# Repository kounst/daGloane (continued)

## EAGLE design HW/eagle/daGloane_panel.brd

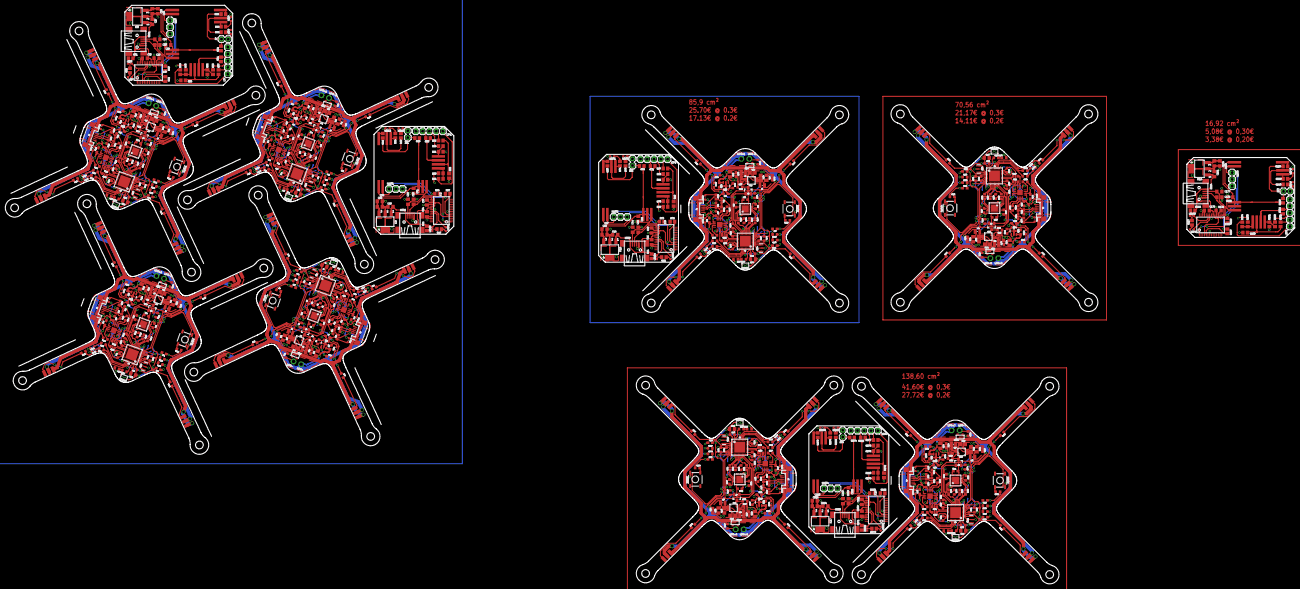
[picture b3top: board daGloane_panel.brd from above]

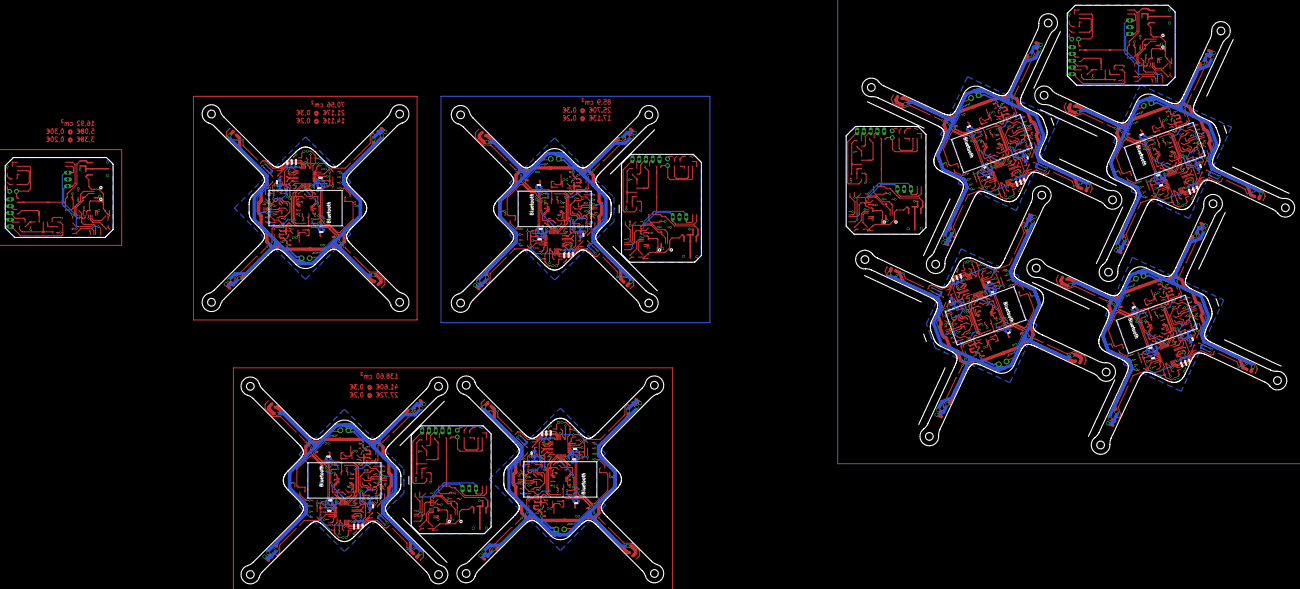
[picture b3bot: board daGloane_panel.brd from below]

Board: 2 copper layers, 484.4 x 217.4 mm, 897 parts (64 on the bottom side), 652 nets.

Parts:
!AT, !AT1, !AT2, !AT3, !AT4: 1X02
BOOTMD, BOOTMD1, BOOTMD2, BOOTMD3, BOOTMD4, BOOTMD5, BOOTMD6, BOOTMD7: 1X02_50MIL
C1, C3, C5, C7, C9, C14, C19, C20, C32, C33, C50, C53, C55, C57, C59, C62, C64, C66, C72, C73, C74, C75, C82, C83, C84, C87, C89, C91, C97, C98, C99, C100, C107, C108, C109, C112, C114, C116, C122, C123, C124, C125, C132, C133, C138, C139, C140, C141, C148, C149, C150, C153, C155, C157, C163, C164, C165, C166, C173, C174, C183, C186, C188, C190, C196, C197, C198, C199, C206, C207, C216, C219, C221, C223, C229, C230, C231, C232, C239, C240: 100nF; C0603
C2, C12, C13, C21, C30, C31, C69, C70, C76, C79, C80, C81, C94, C95, C101, C104, C105, C106, C119, C120, C126, C129, C130, C131, C135, C136, C142, C145, C146, C147, C160, C161, C167, C170, C171, C172, C193, C194, C200, C203, C204, C205, C226, C227, C233, C236, C237, C238: 10µF/6.3V; C0805
C4, C68, C93, C118, C134, C159, C192, C225: 4.7; C0603
C6, C58, C67, C92, C117, C158, C191, C224: 4.7µF; C0603
C8, C10, C71, C78, C96, C103, C121, C128, C137, C144, C162, C169, C195, C202, C228, C235: 1µF; C0603
C11, C16, C54, C63, C77, C88, C102, C113, C127, C143, C154, C168, C187, C201, C220, C234: 10nF; C0603
C15, C56, C65, C90, C115, C156, C189, C222: 2.2nF; C0603
C17, C18, C51, C52, C60, C61, C85, C86, C110, C111, C151, C152, C184, C185, C217, C218: 47pF; C0603
C22, C25, C28, C29, C34, C37, C39, C41, C42, C45, C47, C49, C175, C178, C180, C182, C208, C211, C213, C215: 100nF; C0805
C23, C24, C35, C36, C43, C44, C176, C177, C209, C210: 47pF; C0805
C26, C27, C38, C40, C46, C48, C179, C181, C212, C214: 10µ; C0805
D1, D2, D3, D4, D5, D6, D7, D8: BAT54C; SOT23
GND, GND1, GND2, GND3, GND4, GND5, GND6, GND7: TESTPAD_TPB1,27; TESTPAD_B1,27
IC1, IC4, IC6, IC7, IC11, IC12, IC15, IC18: MCP1252-33X50; MSOP8
IC2, IC3, IC9, IC13, IC16: FT232RL; SSOP28DB
IC5, IC8, IC10, IC14, IC17: UA78M05DCY; SOT223
L1, L2, L3, L4, L5, L6, L7, L8, L9, L10, L11, L12, L13, L14, L15, L16: WUERTH-ELEKTRONIK_WE-KI_0805_B
LED1, LED2, LED3, LED4, LED5, LED6, LED7, LED8, LED9, LED10, LED11, LED12, LED13, LED14, LED15, LED16, LED17, LED18, LED19, LED20, LED21, LED22, LED23, LED24, LED25, LED26, LED27, LED28, LED29, LED30, LED31, LED32, LED33, LED34, LED35, LED36, LED37, LED38, LED39, LED40, LED41, LED42, LED43, LED44, LED45, LED46, LED47, LED48, LED49, LED50, LED51, LED52, LED53, LED54, LED55, LED56, LED57, LED58, LED59, LED60: CHIPLED_0603
LIPO+, LIPO+1, LIPO+2, LIPO+3, LIPO+4, LIPO+5, LIPO+6, LIPO+7: TPSPAD1-13; P1-13
LIPO-, LIPO-1, LIPO-2, LIPO-3, LIPO-4, LIPO-5, LIPO-6, LIPO-7: TPSPAD1-13; P1-13
LTP, LTP1, LTP2, LTP3, LTP4: 1X05
ON/OFF, ON/OFF1, ON/OFF2, ON/OFF3, ON/OFF4, ON/OFF5, ON/OFF6, ON/OFF7: SWITCH-MOMENTARY-2SMD; TACTILE_SWITCH_SMD
R1, R3, R4, R5, R14, R15, R16, R19, R76, R81, R82, R83, R86, R87, R88, R89, R106, R111, R112, R113, R116, R117, R118, R119, R136, R141, R142, R143, R146, R147, R148, R149, R166, R171, R172, R173, R176, R177, R178, R179, R196, R201, R202, R203, R206, R207, R208, R209, R241, R246, R247, R248, R251, R252, R253, R254, R286, R291, R292, R293, R296, R297, R298, R299: 150R; R0603
R2, R92, R122, R152, R182, R212, R257, R302: 2k; R0603
R6, R7, R8, R17, R18, R20, R24, R25, R26, R27, R28, R77, R78, R93, R94, R95, R98, R100, R101, R102, R103, R104, R107, R108, R123, R124, R125, R128, R130, R131, R132, R133, R134, R137, R138, R153, R154, R155, R158, R160, R161, R162, R163, R164, R167, R168, R183, R184, R185, R188, R190, R191, R192, R193, R194, R197, R198, R213, R214, R215, R218, R220, R221, R222, R223, R224, R242, R243, R258, R259, R260, R263, R265, R266, R267, R268, R269, R287, R288, R303, R304, R305, R308, R310, R311, R312, R313, R314: 10k; R0603
R9, R10, R12, R22, R23, R30, R79, R90, R91, R96, R97, R105, R109, R120, R121, R126, R127, R135, R139, R150, R151, R156, R157, R165, R169, R180, R181, R186, R187, R195, R199, R210, R211, R216, R217, R225, R244, R255, R256, R261, R262, R270, R289, R300, R301, R306, R307, R315: 1k; R0603
R11, R13, R84, R85, R114, R115, R144, R145, R174, R175, R204, R205, R249, R250, R294, R295: 27R; R0603
R21, R80, R110, R140, R170, R200, R245, R290: 3k3; R0603
R29, R99, R129, R159, R189, R219, R264, R309: 330; R0603
R31, R32, R46, R47, R61, R62, R226, R227, R271, R272: 150R; R0805
R33, R34, R42, R43, R48, R49, R57, R58, R63, R64, R72, R73, R228, R229, R237, R238, R273, R274, R282, R283: 4k7; R0805
R35, R37, R39, R50, R52, R54, R65, R67, R69, R230, R232, R234, R275, R277, R279: 1k6; R0805
R36, R38, R40, R51, R53, R55, R66, R68, R70, R231, R233, R235, R276, R278, R280: 3k; R0805
R41, R56, R71, R236, R281: 100; R0805
R44, R45, R59, R60, R74, R75, R239, R240, R284, R285: 470R; R0805
SWCLK, SWCLK1, SWCLK2, SWCLK3, SWCLK4, SWCLK5, SWCLK6, SWCLK7: TESTPAD_TPB1,27; TESTPAD_B1,27
SWDIO, SWDIO1, SWDIO2, SWDIO3, SWDIO4, SWDIO5, SWDIO6, SWDIO7: TESTPAD_TPB1,27; TESTPAD_B1,27
U1, U2, U3, U4, U5, U6, U7, U8: STM32F10XTXU6; VFQFPN36
U$1, U$38, U$49, U$60, U$84, U$95, U$118, U$141: MURATA-FILTER_CSTCE__G
U$2, U$37, U$48, U$59, U$83, U$94, U$117, U$140: SPARKFUN_MCP73831; SPARKFUN_SOT23-5
U$3, U$35, U$46, U$57, U$81, U$92, U$115, U$138: MPU6000
U$4, U$36, U$47, U$58, U$82, U$93, U$116, U$139: SERIAL_FT230XQ; SERIAL_QFN4X4-16
U$5, U$40, U$51, U$62, U$86, U$97, U$120, U$143: BLUETOOTH_REDUCED
U$6, U$7, U$8, U$9, U$41, U$42, U$43, U$44, U$52, U$53, U$54, U$55, U$63, U$64, U$65, U$66, U$87, U$88, U$89, U$90, U$98, U$99, U$100, U$101, U$121, U$122, U$123, U$124, U$144, U$145, U$146, U$147: 3A_BLDC_CONTROLLER
U$10, U$39, U$50, U$61, U$85, U$96, U$119, U$142: IRLM6344TRPBF; MICRO3(SOT-23)
U$11, U$45, U$56, U$67, U$91, U$102, U$125, U$148: DAGLOANE_LOGO
U$12, U$13, U$14, U$15, U$16, U$17, U$18, U$19, U$20, U$21, U$22, U$23, U$24, U$25, U$26, U$27, U$28, U$29, U$30, U$31, U$32, U$33, U$34, U$68, U$69, U$70, U$71, U$72, U$73, U$74, U$75, U$76, U$77, U$78, U$79, U$80, U$103, U$104, U$105, U$106, U$107, U$108, U$109, U$110, U$111, U$112, U$113, U$114, U$126, U$127, U$128, U$129, U$130, U$131, U$132, U$133, U$134, U$135, U$136, U$137: SPRING_HEADER
UART, UART1, UART2, UART3, UART4: 1X03
USB1, USB2, USB3, USB4, USB5: USB-MB-S2; USB-MP-S2
X1, X2, X3, X4, X5, X6, X7, X8: USB_MICROB_PLUG_MT; SPARKFUN-CONNECTORS_USB-MICROB

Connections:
+3V1: C38.1, C39.1, C41.1, IC8.3, R49.2, U$26.P$1, U$30.P$1
+3V2: C46.1, C47.1, C49.1, IC10.3, R64.2, U$71.P$1, U$75.P$1
+3V3: C26.1, C28.1, C29.1, IC5.3, R34.2, U$14.P$1, U$18.P$1
+3V4: C179.1, C180.1, C182.1, IC14.3, R229.2, U$105.P$1, U$109.P$1
+3V5: C212.1, C213.1, C215.1, IC17.3, R274.2, U$128.P$1, U$132.P$1
BOOT0: R17.1, U1.35
BOOT1: R168.1, U2.35
BOOT2: R78.1, U3.35
BOOT3: R108.1, U4.35
BOOT4: R138.1, U5.35
BOOT5: R198.1, U6.35
BOOT6: R243.1, U7.35
BOOT7: R288.1, U8.35
CLK: LTP.3, R35.2
CLK1: LTP1.3, R50.2
CLK2: LTP2.3, R65.2
CLK3: LTP3.3, R230.2
CLK4: LTP4.3, R275.2
CSB: LTP.5, R39.2
CSB1: LTP1.5, R54.2
CSB2: LTP2.5, R69.2
CSB3: LTP3.5, R234.2
CSB4: LTP4.5, R279.2
D+: C18.1, R13.1, X2.D+
D+1: C23.1, IC3.15, USB1.D+
D+2: C35.1, IC2.15, USB2.D+
D+3: C60.1, R85.1, X3.D+
D+4: C85.1, R115.1, X4.D+
D+5: C110.1, R145.1, X5.D+
D+6: C43.1, IC9.15, USB3.D+
D+7: C51.1, R175.1, X1.D+
D+8: C151.1, R205.1, X6.D+
D+9: C176.1, IC13.15, USB4.D+
D+10: C184.1, R250.1, X7.D+
D+11: C209.1, IC16.15, USB5.D+
D+12: C217.1, R295.1, X8.D+
D-: C17.1, R11.1, X2.D-
D-1: C24.1, IC3.16, USB1.D-
D-2: C36.1, IC2.16, USB2.D-
D-3: C61.1, R84.1, X3.D-
D-4: C86.1, R114.1, X4.D-
D-5: C111.1, R144.1, X5.D-
D-6: C44.1, IC9.16, USB3.D-
D-7: C52.1, R174.1, X1.D-
D-8: C152.1, R204.1, X6.D-
D-9: C177.1, IC13.16, USB4.D-
D-10: C185.1, R249.1, X7.D-
D-11: C210.1, IC16.16, USB5.D-
D-12: C218.1, R294.1, X8.D-
GND: C1.2, C2.2, C3.2, C4.2, C5.2, C6.1, C7.2, C9.1, C10.2, C11.2, C12.2, C13.2, C14.2, C15.2, C16.2, C17.2, C18.2, C19.2, C20.2, C21.2, C30.2, C31.2, C32.1, C33.1, GND.PP, IC1.4, LED3.C, LED4.C, LIPO-.TP, R2.2, R7.1, R8.1, R20.1, R21.1, R24.1, R28.1, U1.5, U1.18, U1.26, U1.36, U$1.2, U$2.2, U$3.1, U$3.11, U$3.18, U$4.3, U$4.13, U$4.C, U$5.P$13, U$5.P$14, U$5.P$21, U$5.P$22, U$10.2, X2.GND
GND1: !AT.2, C22.1, C23.2, C24.2, C25.2, C26.2, C27.2, C28.2, C29.2, IC3.7, IC3.18, IC3.21, IC3.25, IC3.26, IC5.2, IC5.4, LED8.C, LED9.C, LTP.1, R36.1, R38.1, R40.1, U$15.P$1, UART.2, USB1.GND
GND2: !AT1.2, C34.1, C35.2, C36.2, C37.2, C38.2, C39.2, C40.2, C41.2, IC2.7, IC2.18, IC2.21, IC2.25, IC2.26, IC8.2, IC8.4, LED12.C, LED13.C, LTP1.1, R51.1, R53.1, R55.1, U$27.P$1, UART1.2, USB2.GND
GND3: C59.2, C60.2, C61.2, C62.2, C63.2, C64.2, C65.2, C66.2, C67.1, C68.2, C69.2, C70.2, C72.1, C73.2, C74.2, C75.2, C76.2, C77.2, C78.2, C79.2, C80.2, C81.2, C82.1, C83.1, GND2.PP, IC4.4, LED15.C, LED16.C, LIPO-2.TP, R77.1, R80.1, R92.2, R93.1, R95.1, R98.1, R104.1, U3.5, U3.18, U3.26, U3.36, U$35.1, U$35.11, U$35.18, U$36.3, U$36.13, U$36.C, U$37.2, U$38.2, U$39.2, U$40.P$13, U$40.P$14, U$40.P$21, U$40.P$22, X3.GND
GND4: C84.2, C85.2, C86.2, C87.2, C88.2, C89.2, C90.2, C91.2, C92.1, C93.2, C94.2, C95.2, C97.1, C98.2, C99.2, C100.2, C101.2, C102.2, C103.2, C104.2, C105.2, C106.2, C107.1, C108.1, GND3.PP, IC6.4, LED20.C, LED21.C, LIPO-3.TP, R107.1, R110.1, R122.2, R123.1, R125.1, R128.1, R134.1, U4.5, U4.18, U4.26, U4.36, U$46.1, U$46.11, U$46.18, U$47.3, U$47.13, U$47.C, U$48.2, U$49.2, U$50.2, U$51.P$13, U$51.P$14, U$51.P$21, U$51.P$22, X4.GND
GND5: C109.2, C110.2, C111.2, C112.2, C113.2, C114.2, C115.2, C116.2, C117.1, C118.2, C119.2, C120.2, C122.1, C123.2, C124.2, C125.2, C126.2, C127.2, C128.2, C129.2, C130.2, C131.2, C132.1, C133.1, GND4.PP, IC7.4, LED25.C, LED26.C, LIPO-4.TP, R137.1, R140.1, R152.2, R153.1, R155.1, R158.1, R164.1, U5.5, U5.18, U5.26, U5.36, U$57.1, U$57.11, U$57.18, U$58.3, U$58.13, U$58.C, U$59.2, U$60.2, U$61.2, U$62.P$13, U$62.P$14, U$62.P$21, U$62.P$22, X5.GND
GND6: !AT2.2, C42.1, C43.2, C44.2, C45.2, C46.2, C47.2, C48.2, C49.2, IC9.7, IC9.18, IC9.21, IC9.25, IC9.26, IC10.2, IC10.4, LED31.C, LED32.C, LTP2.1, R66.1, R68.1, R70.1, U$72.P$1, UART2.2, USB3.GND
GND7: C50.2, C51.2, C52.2, C53.2, C54.2, C55.2, C56.2, C57.2, C58.1, C134.2, C135.2, C136.2, C138.1, C139.2, C140.2, C141.2, C142.2, C143.2, C144.2, C145.2, C146.2, C147.2, C148.1, C149.1, GND1.PP, IC11.4, LED33.C, LED34.C, LIPO-1.TP, R167.1, R170.1, R182.2, R183.1, R185.1, R188.1, R194.1, U2.5, U2.18, U2.26, U2.36, U$81.1, U$81.11, U$81.18, U$82.3, U$82.13, U$82.C, U$83.2, U$84.2, U$85.2, U$86.P$13, U$86.P$14, U$86.P$21, U$86.P$22, X1.GND
GND8: C150.2, C151.2, C152.2, C153.2, C154.2, C155.2, C156.2, C157.2, C158.1, C159.2, C160.2, C161.2, C163.1, C164.2, C165.2, C166.2, C167.2, C168.2, C169.2, C170.2, C171.2, C172.2, C173.1, C174.1, GND5.PP, IC12.4, LED38.C, LED39.C, LIPO-5.TP, R197.1, R200.1, R212.2, R213.1, R215.1, R218.1, R224.1, U6.5, U6.18, U6.26, U6.36, U$92.1, U$92.11, U$92.18, U$93.3, U$93.13, U$93.C, U$94.2, U$95.2, U$96.2, U$97.P$13, U$97.P$14, U$97.P$21, U$97.P$22, X6.GND
GND9: !AT3.2, C175.1, C176.2, C177.2, C178.2, C179.2, C180.2, C181.2, C182.2, IC13.7, IC13.18, IC13.21, IC13.25, IC13.26, IC14.2, IC14.4, LED45.C, LED46.C, LTP3.1, R231.1, R233.1, R235.1, U$106.P$1, UART3.2, USB4.GND
GND10: C183.2, C184.2, C185.2, C186.2, C187.2, C188.2, C189.2, C190.2, C191.1, C192.2, C193.2, C194.2, C196.1, C197.2, C198.2, C199.2, C200.2, C201.2, C202.2, C203.2, C204.2, C205.2, C206.1, C207.1, GND6.PP, IC15.4, LED47.C, LED48.C, LIPO-6.TP, R242.1, R245.1, R257.2, R258.1, R260.1, R263.1, R269.1, U7.5, U7.18, U7.26, U7.36, U$115.1, U$115.11, U$115.18, U$116.3, U$116.13, U$116.C, U$117.2, U$118.2, U$119.2, U$120.P$13, U$120.P$14, U$120.P$21, U$120.P$22, X7.GND
GND11: !AT4.2, C208.1, C209.2, C210.2, C211.2, C212.2, C213.2, C214.2, C215.2, IC16.7, IC16.18, IC16.21, IC16.25, IC16.26, IC17.2, IC17.4, LED54.C, LED55.C, LTP4.1, R276.1, R278.1, R280.1, U$129.P$1, UART4.2, USB5.GND
GND12: C216.2, C217.2, C218.2, C219.2, C220.2, C221.2, C222.2, C223.2, C224.1, C225.2, C226.2, C227.2, C229.1, C230.2, C231.2, C232.2, C233.2, C234.2, C235.2, C236.2, C237.2, C238.2, C239.1, C240.1, GND7.PP, IC18.4, LED56.C, LED57.C, LIPO-7.TP, R287.1, R290.1, R302.2, R303.1, R305.1, R308.1, R314.1, U8.5, U8.18, U8.26, U8.36, U$138.1, U$138.11, U$138.18, U$139.3, U$139.13, U$139.C, U$140.2, U$141.2, U$142.2, U$143.P$13, U$143.P$14, U$143.P$21, U$143.P$22, X8.GND
LED1: R15.2, U1.30
LED2: R16.2, U1.29
LED3: R171.2, U2.30
LED4: R166.2, U2.29
LED5: R81.2, U3.30
LED6: R76.2, U3.29
LED7: R111.2, U4.30
LED8: R106.2, U4.29
LED9: R141.2, U5.30
LED10: R136.2, U5.29
LED11: R201.2, U6.30
LED12: R196.2, U6.29
LED13: R246.2, U7.30
LED14: R241.2, U7.29
LED15: R291.2, U8.30
LED16: R286.2, U8.29
LIPO: C4.1, C30.1, C32.2, IC1.8, L2.2, LIPO+.TP, ON/OFF.3, R12.2, U$2.3, U$6.2, U$7.2, U$8.2, U$9.2
LIPO1: C134.1, C146.1, C148.2, IC11.8, L4.2, LIPO+1.TP, ON/OFF1.3, R169.2, U$83.3, U$87.2, U$88.2, U$89.2, U$90.2
LIPO2: C68.1, C80.1, C82.2, IC4.8, L6.2, LIPO+2.TP, ON/OFF2.3, R79.2, U$37.3, U$41.2, U$42.2, U$43.2, U$44.2
LIPO3: C93.1, C105.1, C107.2, IC6.8, L8.2, LIPO+3.TP, ON/OFF3.3, R109.2, U$48.3, U$52.2, U$53.2, U$54.2, U$55.2
LIPO4: C118.1, C130.1, C132.2, IC7.8, L10.2, LIPO+4.TP, ON/OFF4.3, R139.2, U$59.3, U$63.2, U$64.2, U$65.2, U$66.2
LIPO5: C159.1, C171.1, C173.2, IC12.8, L12.2, LIPO+5.TP, ON/OFF5.3, R199.2, U$94.3, U$98.2, U$99.2, U$100.2, U$101.2
LIPO6: C192.1, C204.1, C206.2, IC15.8, L14.2, LIPO+6.TP, ON/OFF6.3, R244.2, U$117.3, U$121.2, U$122.2, U$123.2, U$124.2
LIPO7: C225.1, C237.1, C239.2, IC18.8, L16.2, LIPO+7.TP, ON/OFF7.3, R289.2, U$140.3, U$144.2, U$145.2, U$146.2, U$147.2
MISO: LTP.2, R41.2
MISO1: LTP1.2, R56.2
MISO2: LTP2.2, R71.2
MISO3: LTP3.2, R236.2
MISO4: LTP4.2, R281.2
MOSI: LTP.4, R37.2
MOSI1: LTP1.4, R52.2
MOSI2: LTP2.4, R67.2
MOSI3: LTP3.4, R232.2
MOSI4: LTP4.4, R277.2
MOT1: R18.1, U1.15
MOT2: R27.1, U1.16
MOT3: R25.1, U1.31
MOT4: R26.1, U1.32
MOT5: R192.1, U2.32
MOT6: R190.1, U2.15
MOT7: R193.1, U2.16
MOT8: R191.1, U2.31
MOT9: R102.1, U3.32
MOT10: R100.1, U3.15
MOT11: R103.1, U3.16
MOT12: R101.1, U3.31
MOT13: R132.1, U4.32
MOT14: R130.1, U4.15
MOT15: R133.1, U4.16
MOT16: R131.1, U4.31
MOT17: R162.1, U5.32
MOT18: R160.1, U5.15
MOT19: R163.1, U5.16
MOT20: R161.1, U5.31
MOT21: R222.1, U6.32
MOT22: R220.1, U6.15
MOT23: R223.1, U6.16
MOT24: R221.1, U6.31
MOT25: R267.1, U7.32
MOT26: R265.1, U7.15
MOT27: R268.1, U7.16
MOT28: R266.1, U7.31
MOT29: R312.1, U8.32
MOT30: R310.1, U8.15
MOT31: R313.1, U8.16
MOT32: R311.1, U8.31
MOT_GND: U$6.1, U$7.1, U$8.1, U$9.1, U$10.3
MOT_GND1: U$85.3, U$87.1, U$88.1, U$89.1, U$90.1
MOT_GND2: U$39.3, U$41.1, U$42.1, U$43.1, U$44.1
MOT_GND3: U$50.3, U$52.1, U$53.1, U$54.1, U$55.1
MOT_GND4: U$61.3, U$63.1, U$64.1, U$65.1, U$66.1
MOT_GND5: U$96.3, U$98.1, U$99.1, U$100.1, U$101.1
MOT_GND6: U$119.3, U$121.1, U$122.1, U$123.1, U$124.1
MOT_GND7: U$142.3, U$144.1, U$145.1, U$146.1, U$147.1
unnamed: LED2.C, R19.2
unnamed: U1.2, U$1.3
unnamed: R2.1, U$2.5
unnamed: R5.2, U$3.8
unnamed: C15.1, U$3.20
unnamed: C14.1, U$3.10
unnamed: R22.2, U$5.P$1
unnamed: LED3.A, R15.1
unnamed: LED4.A, R16.1
unnamed: BOOTMD.2, R17.2, R20.2
unnamed: R14.1, U$4.11
unnamed: R19.1, U$4.5
unnamed: R4.2, U$3.23
unnamed: LED1.C, R14.2
unnamed: R23.2, U$5.P$2
unnamed: R11.2, U$4.7
unnamed: R13.2, U$4.6
unnamed: R3.2, U$3.9
unnamed: R1.2, U$3.24
unnamed: R9.1, U$4.15
unnamed: R10.1, U$4.2
unnamed: R18.2, U$6.3
unnamed: D3.2, ON/OFF.1, R6.1, R7.2
unnamed: C8.2, IC1.6
unnamed: U1.3, U$1.1
unnamed: R30.1, U$5.P$34
unnamed: IC3.23, LED6.C
unnamed: C8.1, IC1.5
unnamed: IC3.22, LED7.C
unnamed: LED6.A, R31.1
unnamed: LED7.A, R32.1
unnamed: R33.1, U$21.P$1
unnamed: !AT.1, R33.2, R34.1
unnamed: R39.1, R40.2, U$17.P$1
unnamed: R37.1, R38.2, U$19.P$1
unnamed: R35.1, R36.2, U$20.P$1
unnamed: R41.1, U$16.P$1
unnamed: R27.2, U$7.3
unnamed: R25.2, U$8.3
unnamed: R26.2, U$9.3
unnamed: R42.1, U$12.P$1, UART.3
unnamed: R29.2, U$2.1
unnamed: LED5.C, R29.1
unnamed: C12.1, IC1.3, L2.1
unnamed: C13.1, IC1.2, L1.2
unnamed: R43.1, U$13.P$1, UART.1
unnamed: LED8.A, R44.1
unnamed: LED9.A, R45.1
unnamed: R44.2, U$23.P$1
unnamed: R45.2, U$22.P$1
unnamed: IC2.23, LED10.C
unnamed: IC2.22, LED11.C
unnamed: LED10.A, R46.1
unnamed: LED11.A, R47.1
unnamed: R48.1, U$33.P$1
unnamed: !AT1.1, R48.2, R49.1
unnamed: R54.1, R55.2, U$29.P$1
unnamed: R52.1, R53.2, U$31.P$1
unnamed: R50.1, R51.2, U$32.P$1
unnamed: R56.1, U$28.P$1
unnamed: R57.1, U$24.P$1, UART1.3
unnamed: R58.1, U$25.P$1, UART1.1
unnamed: LED12.A, R59.1
unnamed: LED13.A, R60.1
unnamed: R59.2, U$68.P$1
unnamed: R60.2, U$34.P$1
unnamed: IC9.23, LED14.C
unnamed: IC9.22, LED30.C
unnamed: LED14.A, R61.1
unnamed: LED30.A, R62.1
unnamed: R63.1, U$78.P$1
unnamed: !AT2.1, R63.2, R64.1
unnamed: R69.1, R70.2, U$74.P$1
unnamed: R67.1, R68.2, U$76.P$1
unnamed: R65.1, R66.2, U$77.P$1
unnamed: R71.1, U$73.P$1
unnamed: R72.1, U$69.P$1, UART2.3
unnamed: R73.1, U$70.P$1, UART2.1
unnamed: LED31.A, R74.1
unnamed: LED32.A, R75.1
unnamed: R74.2, U$80.P$1
unnamed: R75.2, U$79.P$1
unnamed: BOOTMD1.2, R167.2, R168.2
unnamed: BOOTMD2.2, R77.2, R78.2
unnamed: LED16.A, R76.1
unnamed: LED15.A, R81.1
unnamed: R82.1, U$36.11
unnamed: R83.1, U$36.5
unnamed: R84.2, U$36.7
unnamed: R85.2, U$36.6
unnamed: C65.1, U$35.20
unnamed: C66.1, U$35.10
unnamed: R89.2, U$35.8
unnamed: R88.2, U$35.23
unnamed: R87.2, U$35.9
unnamed: R86.2, U$35.24
unnamed: R90.1, U$36.15
unnamed: R91.1, U$36.2
unnamed: R92.1, U$37.5
unnamed: C71.1, IC4.5
unnamed: C71.2, IC4.6
unnamed: D2.2, ON/OFF2.1, R93.2, R94.1
unnamed: U3.2, U$38.3
unnamed: U3.3, U$38.1
unnamed: LED18.C, R83.2
unnamed: LED17.C, R82.2
unnamed: R96.2, U$40.P$1
unnamed: R97.2, U$40.P$2
unnamed: R99.2, U$37.1
unnamed: LED19.C, R99.1
unnamed: C70.1, IC4.3, L6.1
unnamed: C69.1, IC4.2, L5.2
unnamed: R100.2, U$41.3
unnamed: R103.2, U$42.3
unnamed: R101.2, U$43.3
unnamed: R102.2, U$44.3
unnamed: R105.1, U$40.P$34
unnamed: BOOTMD3.2, R107.2, R108.2
unnamed: LED21.A, R106.1
unnamed: LED20.A, R111.1
unnamed: R112.1, U$47.11
unnamed: R113.1, U$47.5
unnamed: R114.2, U$47.7
unnamed: R115.2, U$47.6
unnamed: C90.1, U$46.20
unnamed: C91.1, U$46.10
unnamed: R119.2, U$46.8
unnamed: R118.2, U$46.23
unnamed: R117.2, U$46.9
unnamed: R116.2, U$46.24
unnamed: R120.1, U$47.15
unnamed: R121.1, U$47.2
unnamed: R122.1, U$48.5
unnamed: C96.1, IC6.5
unnamed: C96.2, IC6.6
unnamed: D4.2, ON/OFF3.1, R123.2, R124.1
unnamed: U4.2, U$49.3
unnamed: U4.3, U$49.1
unnamed: LED23.C, R113.2
unnamed: LED22.C, R112.2
unnamed: R126.2, U$51.P$1
unnamed: R127.2, U$51.P$2
unnamed: R129.2, U$48.1
unnamed: LED24.C, R129.1
unnamed: C95.1, IC6.3, L8.1
unnamed: C94.1, IC6.2, L7.2
unnamed: R130.2, U$52.3
unnamed: R133.2, U$53.3
unnamed: R131.2, U$54.3
unnamed: R132.2, U$55.3
unnamed: R135.1, U$51.P$34
unnamed: BOOTMD4.2, R137.2, R138.2
unnamed: LED26.A, R136.1
unnamed: LED25.A, R141.1
unnamed: R142.1, U$58.11
unnamed: R143.1, U$58.5
unnamed: R144.2, U$58.7
unnamed: R145.2, U$58.6
unnamed: C115.1, U$57.20
unnamed: C116.1, U$57.10
unnamed: R149.2, U$57.8
unnamed: R148.2, U$57.23
unnamed: R147.2, U$57.9
unnamed: R146.2, U$57.24
unnamed: R150.1, U$58.15
unnamed: R151.1, U$58.2
unnamed: R152.1, U$59.5
unnamed: C121.1, IC7.5
unnamed: C121.2, IC7.6
unnamed: D5.2, ON/OFF4.1, R153.2, R154.1
unnamed: U5.2, U$60.3
unnamed: U5.3, U$60.1
unnamed: LED28.C, R143.2
unnamed: LED27.C, R142.2
unnamed: R156.2, U$62.P$1
unnamed: R157.2, U$62.P$2
unnamed: R159.2, U$59.1
unnamed: LED29.C, R159.1
unnamed: C120.1, IC7.3, L10.1
unnamed: C119.1, IC7.2, L9.2
unnamed: R160.2, U$63.3
unnamed: R163.2, U$64.3
unnamed: R161.2, U$65.3
unnamed: R162.2, U$66.3
unnamed: R165.1, U$62.P$34
unnamed: LED34.A, R166.1
unnamed: LED33.A, R171.1
unnamed: R172.1, U$82.11
unnamed: R173.1, U$82.5
unnamed: R174.2, U$82.7
unnamed: R175.2, U$82.6
unnamed: C56.1, U$81.20
unnamed: C57.1, U$81.10
unnamed: R179.2, U$81.8
unnamed: R178.2, U$81.23
unnamed: R177.2, U$81.9
unnamed: R176.2, U$81.24
unnamed: R180.1, U$82.15
unnamed: R181.1, U$82.2
unnamed: R182.1, U$83.5
unnamed: C137.1, IC11.5
unnamed: C137.2, IC11.6
unnamed: D1.2, ON/OFF1.1, R183.2, R184.1
unnamed: U2.2, U$84.3
unnamed: U2.3, U$84.1
unnamed: LED36.C, R173.2
unnamed: LED35.C, R172.2
unnamed: R186.2, U$86.P$1
unnamed: R187.2, U$86.P$2
unnamed: R189.2, U$83.1
unnamed: LED37.C, R189.1
unnamed: C136.1, IC11.3, L4.1
unnamed: C135.1, IC11.2, L3.2
unnamed: R190.2, U$87.3
unnamed: R193.2, U$88.3
unnamed: R191.2, U$89.3
unnamed: R192.2, U$90.3
unnamed: R195.1, U$86.P$34
unnamed: BOOTMD5.2, R197.2, R198.2
unnamed: LED39.A, R196.1
unnamed: LED38.A, R201.1
unnamed: R202.1, U$93.11
unnamed: R203.1, U$93.5
unnamed: R204.2, U$93.7
unnamed: R205.2, U$93.6
unnamed: C156.1, U$92.20
unnamed: C157.1, U$92.10
unnamed: R209.2, U$92.8
unnamed: R208.2, U$92.23
unnamed: R207.2, U$92.9
unnamed: R206.2, U$92.24
unnamed: R210.1, U$93.15
unnamed: R211.1, U$93.2
unnamed: R212.1, U$94.5
unnamed: C162.1, IC12.5
unnamed: C162.2, IC12.6
unnamed: D6.2, ON/OFF5.1, R213.2, R214.1
unnamed: U6.2, U$95.3
unnamed: U6.3, U$95.1
unnamed: LED41.C, R203.2
unnamed: LED40.C, R202.2
unnamed: R216.2, U$97.P$1
unnamed: R217.2, U$97.P$2
unnamed: R219.2, U$94.1
unnamed: LED42.C, R219.1
unnamed: C161.1, IC12.3, L12.1
unnamed: C160.1, IC12.2, L11.2
unnamed: R220.2, U$98.3
unnamed: R223.2, U$99.3
unnamed: R221.2, U$100.3
unnamed: R222.2, U$101.3
unnamed: R225.1, U$97.P$34
unnamed: IC13.23, LED43.C
unnamed: IC13.22, LED44.C
unnamed: LED43.A, R226.1
unnamed: LED44.A, R227.1
unnamed: R228.1, U$112.P$1
unnamed: !AT3.1, R228.2, R229.1
unnamed: R234.1, R235.2, U$108.P$1
unnamed: R232.1, R233.2, U$110.P$1
unnamed: R230.1, R231.2, U$111.P$1
unnamed: R236.1, U$107.P$1
unnamed: R237.1, U$103.P$1, UART3.3
unnamed: R238.1, U$104.P$1, UART3.1
unnamed: LED45.A, R239.1
unnamed: LED46.A, R240.1
unnamed: R239.2, U$114.P$1
unnamed: R240.2, U$113.P$1
unnamed: BOOTMD6.2, R242.2, R243.2
unnamed: LED48.A, R241.1
unnamed: LED47.A, R246.1
unnamed: R247.1, U$116.11
unnamed: R248.1, U$116.5
unnamed: R249.2, U$116.7
unnamed: R250.2, U$116.6
unnamed: C189.1, U$115.20
unnamed: C190.1, U$115.10
unnamed: R254.2, U$115.8
unnamed: R253.2, U$115.23
unnamed: R252.2, U$115.9
unnamed: R251.2, U$115.24
unnamed: R255.1, U$116.15
unnamed: R256.1, U$116.2
unnamed: R257.1, U$117.5
unnamed: C195.1, IC15.5
unnamed: C195.2, IC15.6
unnamed: D7.2, ON/OFF6.1, R258.2, R259.1
unnamed: U7.2, U$118.3
unnamed: U7.3, U$118.1
unnamed: LED50.C, R248.2
unnamed: LED49.C, R247.2
unnamed: R261.2, U$120.P$1
unnamed: R262.2, U$120.P$2
unnamed: R264.2, U$117.1
unnamed: LED51.C, R264.1
unnamed: C194.1, IC15.3, L14.1
unnamed: C193.1, IC15.2, L13.2
unnamed: R265.2, U$121.3
unnamed: R268.2, U$122.3
unnamed: R266.2, U$123.3
unnamed: R267.2, U$124.3
unnamed: R270.1, U$120.P$34
unnamed: IC16.23, LED52.C
unnamed: IC16.22, LED53.C
unnamed: LED52.A, R271.1
unnamed: LED53.A, R272.1
unnamed: R273.1, U$135.P$1
unnamed: !AT4.1, R273.2, R274.1
unnamed: R279.1, R280.2, U$131.P$1
unnamed: R277.1, R278.2, U$133.P$1
unnamed: R275.1, R276.2, U$134.P$1
unnamed: R281.1, U$130.P$1
unnamed: R282.1, U$126.P$1, UART4.3
unnamed: R283.1, U$127.P$1, UART4.1
unnamed: LED54.A, R284.1
unnamed: LED55.A, R285.1
unnamed: R284.2, U$137.P$1
unnamed: R285.2, U$136.P$1
unnamed: BOOTMD7.2, R287.2, R288.2
unnamed: LED57.A, R286.1
unnamed: LED56.A, R291.1
unnamed: R292.1, U$139.11
unnamed: R293.1, U$139.5
unnamed: R294.2, U$139.7
unnamed: R295.2, U$139.6
unnamed: C222.1, U$138.20
unnamed: C223.1, U$138.10
unnamed: R299.2, U$138.8
unnamed: R298.2, U$138.23
unnamed: R297.2, U$138.9
unnamed: R296.2, U$138.24
unnamed: R300.1, U$139.15
unnamed: R301.1, U$139.2
unnamed: R302.1, U$140.5
unnamed: C228.1, IC18.5
unnamed: C228.2, IC18.6
unnamed: D8.2, ON/OFF7.1, R303.2, R304.1
unnamed: U8.2, U$141.3
unnamed: U8.3, U$141.1
unnamed: LED59.C, R293.2
unnamed: LED58.C, R292.2
unnamed: R306.2, U$143.P$1
unnamed: R307.2, U$143.P$2
unnamed: R309.2, U$140.1
unnamed: LED60.C, R309.1
unnamed: C227.1, IC18.3, L16.1
unnamed: C226.1, IC18.2, L15.2
unnamed: R310.2, U$144.3
unnamed: R313.2, U$145.3
unnamed: R311.2, U$146.3
unnamed: R312.2, U$147.3
unnamed: R315.1, U$143.P$34
PWR_OFF: R6.2, R30.2, U1.8
PWR_OFF1: R184.2, R195.2, U2.8
PWR_OFF2: R94.2, R105.2, U3.8
PWR_OFF3: R124.2, R135.2, U4.8
PWR_OFF4: R154.2, R165.2, U5.8
PWR_OFF5: R214.2, R225.2, U6.8
PWR_OFF6: R259.2, R270.2, U7.8
PWR_OFF7: R304.2, R315.2, U8.8
PWR_ON: D3.3, IC1.7, R8.2
PWR_ON1: D1.3, IC11.7, R185.2
PWR_ON2: D2.3, IC4.7, R95.2
PWR_ON3: D4.3, IC6.7, R125.2
PWR_ON4: D5.3, IC7.7, R155.2
PWR_ON5: D6.3, IC12.7, R215.2
PWR_ON6: D7.3, IC15.7, R260.2
PWR_ON7: D8.3, IC18.7, R305.2
PWR_ON_µC: D3.1, R28.2, U1.17
PWR_ON_µC1: D1.1, R194.2, U2.17
PWR_ON_µC2: D2.1, R104.2, U3.17
PWR_ON_µC3: D4.1, R134.2, U4.17
PWR_ON_µC4: D5.1, R164.2, U5.17
PWR_ON_µC5: D6.1, R224.2, U6.17
PWR_ON_µC6: D7.1, R269.2, U7.17
PWR_ON_µC7: D8.1, R314.2, U8.17
RESET1: C9.2, U1.4
RESET2: C138.2, U2.4
RESET3: C72.2, U3.4
RESET4: C97.2, U4.4
RESET5: C122.2, U5.4
RESET6: C163.2, U6.4
RESET7: C196.2, U7.4
RESET8: C229.2, U8.4
SPI1_CS: R5.1, U1.11
SPI1_CS1: R179.1, U2.11
SPI1_CS2: R89.1, U3.11
SPI1_CS3: R119.1, U4.11
SPI1_CS4: R149.1, U5.11
SPI1_CS5: R209.1, U6.11
SPI1_CS6: R254.1, U7.11
SPI1_CS7: R299.1, U8.11
SPI1_MISO: R3.1, U1.13
SPI1_MISO1: R177.1, U2.13
SPI1_MISO2: R87.1, U3.13
SPI1_MISO3: R117.1, U4.13
SPI1_MISO4: R147.1, U5.13
SPI1_MISO5: R207.1, U6.13
SPI1_MISO6: R252.1, U7.13
SPI1_MISO7: R297.1, U8.13
SPI1_MOSI: R1.1, U1.14
SPI1_MOSI1: R176.1, U2.14
SPI1_MOSI2: R86.1, U3.14
SPI1_MOSI3: R116.1, U4.14
SPI1_MOSI4: R146.1, U5.14
SPI1_MOSI5: R206.1, U6.14
SPI1_MOSI6: R251.1, U7.14
SPI1_MOSI7: R296.1, U8.14
SPI1_SCK: R4.1, U1.12
SPI1_SCK1: R178.1, U2.12
SPI1_SCK2: R88.1, U3.12
SPI1_SCK3: R118.1, U4.12
SPI1_SCK4: R148.1, U5.12
SPI1_SCK5: R208.1, U6.12
SPI1_SCK6: R253.1, U7.12
SPI1_SCK7: R298.1, U8.12
SWCLK: SWCLK.PP, U1.28
SWCLK1: SWCLK1.PP, U2.28
SWCLK2: SWCLK2.PP, U3.28
SWCLK3: SWCLK3.PP, U4.28
SWCLK4: SWCLK4.PP, U5.28
SWCLK5: SWCLK5.PP, U6.28
SWCLK6: SWCLK6.PP, U7.28
SWCLK7: SWCLK7.PP, U8.28
SWDIO: SWDIO.PP, U1.25
SWDIO1: SWDIO1.PP, U2.25
SWDIO2: SWDIO2.PP, U3.25
SWDIO3: SWDIO3.PP, U4.25
SWDIO4: SWDIO4.PP, U5.25
SWDIO5: SWDIO5.PP, U6.25
SWDIO6: SWDIO6.PP, U7.25
SWDIO7: SWDIO7.PP, U8.25
USART1_RX: R9.2, U1.22
USART1_RX1: R180.2, U2.22
USART1_RX2: R90.2, U3.22
USART1_RX3: R120.2, U4.22
USART1_RX4: R150.2, U5.22
USART1_RX5: R210.2, U6.22
USART1_RX6: R255.2, U7.22
USART1_RX7: R300.2, U8.22
USART1_TX: R10.2, U1.21
USART1_TX1: R181.2, U2.21
USART1_TX2: R91.2, U3.21
USART1_TX3: R121.2, U4.21
USART1_TX4: R151.2, U5.21
USART1_TX5: R211.2, U6.21
USART1_TX6: R256.2, U7.21
USART1_TX7: R301.2, U8.21
USART2_RX: R22.1, U1.10
USART2_RX1: R186.1, U2.10
USART2_RX2: R96.1, U3.10
USART2_RX3: R126.1, U4.10
USART2_RX4: R156.1, U5.10
USART2_RX5: R216.1, U6.10
USART2_RX6: R261.1, U7.10
USART2_RX7: R306.1, U8.10
USART2_TX: R23.1, U1.9
USART2_TX1: R187.1, U2.9
USART2_TX2: R97.1, U3.9
USART2_TX3: R127.1, U4.9
USART2_TX4: R157.1, U5.9
USART2_TX5: R217.1, U6.9
USART2_TX6: R262.1, U7.9
USART2_TX7: R307.1, U8.9
USART_RX: IC3.1, R43.2
USART_RX1: IC2.1, R58.2
USART_RX2: IC9.1, R73.2
USART_RX3: IC13.1, R238.2
USART_RX4: IC16.1, R283.2
USART_TX: IC3.5, R42.2
USART_TX1: IC2.5, R57.2
USART_TX2: IC9.5, R72.2
USART_TX3: IC13.5, R237.2
USART_TX4: IC16.5, R282.2
VBUS: C6.2, C16.1, LED5.A, U$2.4, U$4.10, X2.VBUS
VBUS1: C54.1, C58.2, LED37.A, U$82.10, U$83.4, X1.VBUS
VBUS2: C63.1, C67.2, LED19.A, U$36.10, U$37.4, X3.VBUS
VBUS3: C88.1, C92.2, LED24.A, U$47.10, U$48.4, X4.VBUS
VBUS4: C113.1, C117.2, LED29.A, U$58.10, U$59.4, X5.VBUS
VBUS5: C154.1, C158.2, LED42.A, U$93.10, U$94.4, X6.VBUS
VBUS6: C187.1, C191.2, LED51.A, U$116.10, U$117.4, X7.VBUS
VBUS7: C220.1, C224.2, LED60.A, U$139.10, U$140.4, X8.VBUS
VCC: BOOTMD.1, C1.1, C2.1, C3.1, C5.1, C7.1, C10.1, C11.1, C21.1, C31.1, C33.2, L1.1, R24.2, U1.1, U1.6, U1.19, U1.27, U$3.13, U$5.P$11, U$5.P$12, U$10.1
VCC1: BOOTMD1.1, C55.1, C139.1, C140.1, C141.1, C142.1, C143.1, C144.1, C145.1, C147.1, C149.2, L3.1, R188.2, U2.1, U2.6, U2.19, U2.27, U$81.13, U$85.1, U$86.P$11, U$86.P$12
VCC2: BOOTMD2.1, C64.1, C73.1, C74.1, C75.1, C76.1, C77.1, C78.1, C79.1, C81.1, C83.2, L5.1, R98.2, U3.1, U3.6, U3.19, U3.27, U$35.13, U$39.1, U$40.P$11, U$40.P$12
VCC3: BOOTMD3.1, C89.1, C98.1, C99.1, C100.1, C101.1, C102.1, C103.1, C104.1, C106.1, C108.2, L7.1, R128.2, U4.1, U4.6, U4.19, U4.27, U$46.13, U$50.1, U$51.P$11, U$51.P$12
VCC4: BOOTMD4.1, C114.1, C123.1, C124.1, C125.1, C126.1, C127.1, C128.1, C129.1, C131.1, C133.2, L9.1, R158.2, U5.1, U5.6, U5.19, U5.27, U$57.13, U$61.1, U$62.P$11, U$62.P$12
VCC5: BOOTMD5.1, C155.1, C164.1, C165.1, C166.1, C167.1, C168.1, C169.1, C170.1, C172.1, C174.2, L11.1, R218.2, U6.1, U6.6, U6.19, U6.27, U$92.13, U$96.1, U$97.P$11, U$97.P$12
VCC6: BOOTMD6.1, C188.1, C197.1, C198.1, C199.1, C200.1, C201.1, C202.1, C203.1, C205.1, C207.2, L13.1, R263.2, U7.1, U7.6, U7.19, U7.27, U$115.13, U$119.1, U$120.P$11, U$120.P$12
VCC7: BOOTMD7.1, C221.1, C230.1, C231.1, C232.1, C233.1, C234.1, C235.1, C236.1, C238.1, C240.2, L15.1, R308.2, U8.1, U8.6, U8.19, U8.27, U$138.13, U$142.1, U$143.P$11, U$143.P$12
VCCIO: C19.1, LED1.A, LED2.A, U$4.1, U$4.8, U$4.9
VCCIO1: C53.1, LED35.A, LED36.A, U$82.1, U$82.8, U$82.9
VCCIO2: C62.1, LED17.A, LED18.A, U$36.1, U$36.8, U$36.9
VCCIO3: C87.1, LED22.A, LED23.A, U$47.1, U$47.8, U$47.9
VCCIO4: C112.1, LED27.A, LED28.A, U$58.1, U$58.8, U$58.9
VCCIO5: C153.1, LED40.A, LED41.A, U$93.1, U$93.8, U$93.9
VCCIO6: C186.1, LED49.A, LED50.A, U$116.1, U$116.8, U$116.9
VCCIO7: C219.1, LED58.A, LED59.A, U$139.1, U$139.8, U$139.9
VDD5.0: C22.2, C27.1, IC3.20, IC5.1, R31.2, R32.2, USB1.VBUS
VDD5.1: C34.2, C40.1, IC2.20, IC8.1, R46.2, R47.2, USB2.VBUS
VDD5.2: C42.2, C48.1, IC9.20, IC10.1, R61.2, R62.2, USB3.VBUS
VDD5.3: C175.2, C181.1, IC13.20, IC14.1, R226.2, R227.2, USB4.VBUS
VDD5.4: C208.2, C214.1, IC16.20, IC17.1, R271.2, R272.2, USB5.VBUS
VDDIO: C25.1, IC3.4, IC3.17, IC3.19
VDDIO1: C37.1, IC2.4, IC2.17, IC2.19
VDDIO2: C45.1, IC9.4, IC9.17, IC9.19
VDDIO3: C178.1, IC13.4, IC13.17, IC13.19
VDDIO4: C211.1, IC16.4, IC16.17, IC16.19
VOLTAGE: C20.1, R12.1, R21.2, U1.7
VOLTAGE1: C50.1, R169.1, R170.2, U2.7
VOLTAGE2: C59.1, R79.1, R80.2, U3.7
VOLTAGE3: C84.1, R109.1, R110.2, U4.7
VOLTAGE4: C109.1, R139.1, R140.2, U5.7
VOLTAGE5: C150.1, R199.1, R200.2, U6.7
VOLTAGE6: C183.1, R244.1, R245.2, U7.7
VOLTAGE7: C216.1, R289.1, R290.2, U8.7

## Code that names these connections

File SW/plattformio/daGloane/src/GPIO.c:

/*
 * GPIO.c
 *
 *  Created on: Nov 13, 2010
 *      Author: konstantin
 */


/* Includes ------------------------------------------------------------------*/
//#include "stm32f10x.h"
#include "stm32f1xx_hal.h"
#include "GPIO.h"
//#include "uAC.h"


void GPIO_Configuration(void)
{
	GPIO_InitTypeDef GPIO_InitStructure;

	__HAL_AFIO_REMAP_SWJ_NOJTAG();
	__HAL_AFIO_REMAP_TIM3_PARTIAL();
	__HAL_AFIO_REMAP_TIM2_PARTIAL_1();
	// GPIO_PinRemapConfig(GPIO_Remap_SWJ_JTAGDisable, ENABLE);
	// GPIO_PinRemapConfig(GPIO_PartialRemap_TIM3, ENABLE);
	// GPIO_PinRemapConfig(GPIO_PartialRemap1_TIM2, ENABLE);

//   GPIO_InitTypeDef GPIO_InitStruct;
  
//   GPIO_InitStruct.Pin = GPIO_PIN_15;
//   GPIO_InitStruct.Mode = GPIO_MODE_OUTPUT_PP;
//   GPIO_InitStruct.Pull = GPIO_PULLUP;
//   GPIO_InitStruct.Speed = GPIO_SPEED_FREQ_HIGH;
//   HAL_GPIO_Init(GPIOA, &GPIO_InitStruct); 

//   GPIO_InitStruct.Pin = GPIO_PIN_3;
//   HAL_GPIO_Init(GPIOB, &GPIO_InitStruct); 

//   GPIO_InitStruct.Pin = GPIO_PIN_2;
//   HAL_GPIO_Init(GPIOB, &GPIO_InitStruct);   


	/* LED1 & LED2 */
	GPIO_InitStructure.Pin = LED1_PIN;
	//GPIO_InitStructure.GPIO_Mode = GPIO_Mode_AF_PP;
	GPIO_InitStructure.Mode = GPIO_MODE_OUTPUT_PP;
	GPIO_InitStructure.Speed = GPIO_SPEED_FREQ_HIGH;
	HAL_GPIO_Init(LED1_GPIO_PORT, &GPIO_InitStructure);

	GPIO_InitStructure.Pin = LED2_PIN;
	HAL_GPIO_Init(LED2_GPIO_PORT, &GPIO_InitStructure);

//	LEDOff(LED1);
//	LEDOff(LED2);

	/* Power_ON_�C */
	GPIO_InitStructure.Mode = GPIO_MODE_OUTPUT_PP;
	GPIO_InitStructure.Pin = GPIO_PIN_2;
	HAL_GPIO_Init(GPIOB, &GPIO_InitStructure);

	/* Power_OFF */
	GPIO_InitStructure.Pin = GPIO_PIN_1;
	GPIO_InitStructure.Mode = GPIO_MODE_INPUT;
	HAL_GPIO_Init(GPIOA, &GPIO_InitStructure);

	/* MotorPWM 1..4 */
	GPIO_InitStructure.Mode = GPIO_MODE_AF_PP;
	GPIO_InitStructure.Pin = GPIO_PIN_0;
	HAL_GPIO_Init(GPIOB, &GPIO_InitStructure);

	GPIO_InitStructure.Pin = GPIO_PIN_1;
	HAL_GPIO_Init(GPIOB, &GPIO_InitStructure);

	GPIO_InitStructure.Pin = GPIO_PIN_4;
	HAL_GPIO_Init(GPIOB, &GPIO_InitStructure);

	GPIO_InitStructure.Pin = GPIO_PIN_5;
	HAL_GPIO_Init(GPIOB, &GPIO_InitStructure);

	/* SPI Pin Configuration */
	/* SPI_CLK, SPI_MOSI and MISO */
	GPIO_InitStructure.Mode = GPIO_MODE_AF_PP;
	GPIO_InitStructure.Pin = GPIO_PIN_5 | GPIO_PIN_7;
	HAL_GPIO_Init(GPIOA, &GPIO_InitStructure);
	/* SPI_CS */
	GPIO_InitStructure.Mode = GPIO_MODE_OUTPUT_PP;
	GPIO_InitStructure.Pin = GPIO_PIN_4;
	HAL_GPIO_Init(GPIOA, &GPIO_InitStructure);

	GPIO_InitStructure.Mode = GPIO_MODE_INPUT;
	GPIO_InitStructure.Pull = GPIO_PULLDOWN;
	GPIO_InitStructure.Pin = GPIO_PIN_6;
	HAL_GPIO_Init(GPIOA, &GPIO_InitStructure);

	/* Voltage pin PA0 */
	GPIO_InitStructure.Pin = GPIO_PIN_0;
	GPIO_InitStructure.Mode = GPIO_MODE_ANALOG;
	GPIO_InitStructure.Speed = GPIO_SPEED_FREQ_HIGH;
	HAL_GPIO_Init(GPIOA, &GPIO_InitStructure);

	/* Configure USART1 Tx (PA9) as alternate function push-pull */
	GPIO_InitStructure.Pin = GPIO_PIN_9;
	GPIO_InitStructure.Speed = GPIO_SPEED_FREQ_LOW;
	GPIO_InitStructure.Mode = GPIO_MODE_AF_PP;
	HAL_GPIO_Init(GPIOA, &GPIO_InitStructure);

	/* Configure USART1 Rx (PA10) as input floating */
	GPIO_InitStructure.Pin = GPIO_PIN_10;
	GPIO_InitStructure.Pull = GPIO_NOPULL;
	GPIO_InitStructure.Mode = GPIO_MODE_INPUT;
	HAL_GPIO_Init(GPIOA, &GPIO_InitStructure);

	/* Configure USART2 Tx (PA2) as alternate function push-pull */
	GPIO_InitStructure.Pin = GPIO_PIN_2;
	GPIO_InitStructure.Speed = GPIO_SPEED_FREQ_LOW;
	GPIO_InitStructure.Mode = GPIO_MODE_AF_PP;
	HAL_GPIO_Init(GPIOA, &GPIO_InitStructure);

	/* Configure USART2 Rx (PA3) as input floating */
	GPIO_InitStructure.Pin = GPIO_PIN_3;
	GPIO_InitStructure.Pull = GPIO_NOPULL;
	GPIO_InitStructure.Mode = GPIO_MODE_INPUT;
	HAL_GPIO_Init(GPIOA, &GPIO_InitStructure);

}


void PWR_Buttom_handler()
{
	static uint16_t TurnOff_count = 250;

	if(debounce(GPIOA->IDR & 2))		//tactile switch input
	{
		if(TurnOff_count)
		{
			TurnOff_count--;
			if(!(TurnOff_count % 100))
				uac_printf("TurnOff_count: %i\n", TurnOff_count/100);
			if(!TurnOff_count)
				uac_printf("\nBye-bye!\n");
		}
	}
	else
	{
		if(!TurnOff_count)
		{
			GPIOB->BRR = GPIO_PIN_2;	//turn off DCDC
		}
		else
		{
			TurnOff_count = 250;		//reset TurnOff delay
		}
	}
}


/**
 * @brief  Debounces a digital input.
 * @param  IOstate: Specifies the raw input state seen on the input port pin.

 * @retval 0, 1 this is the debounced input state
 */
uint8_t debounce(uint16_t IOstate)
{
	static uint32_t state = 0;
	static uint16_t debounce = 0;

	if(IOstate != 0)
		IOstate = 1;

	state = (state<<1) | IOstate;

	if(state == 0)
		debounce = 0;
	if(state == 0xFFFFFFFF)
		debounce = 1;

	return debounce;
}

/**
 * @brief  Toggles LED1 with 1Hz 50% duty cycle
 * @param  none
 * @retval none
 */
void HeartBeat(void)
{
	static uint16_t heart_count = 0;
	static uint8_t fade_dir = 1;

	if(fade_dir)
		heart_count++;
	else
		heart_count--;

	if(heart_count == 1000)
	{
		fade_dir = 0;
	}
	if(heart_count == 0)
		fade_dir = 1;

	TIM_SetCompare2(TIM2, heart_count*32);

}


const uint16_t GPIO_PIN[2] = {LED1_PIN, LED2_PIN};
GPIO_TypeDef* GPIO_PORT[2] = {LED1_GPIO_PORT, LED2_GPIO_PORT};

/**
 * @brief  Toggles the selected LED.
 * @param  Led: Specifies the Led to be toggled.
 *   This parameter can be one of following parameters:
 *     @arg LED1
 *     @arg LED2
 * @retval None
 */
void LEDToggle(Led_TypeDef Led)
{
	GPIO_PORT[Led]->ODR ^= GPIO_PIN[Led];
}

/**
 * @brief  Turns selected LED On.
 * @param  Led: Specifies the Led to be set on.
 *   This parameter can be one of following parameters:
 *     @arg LED1
 *     @arg LED2
 * @retval None
 */
void LEDOn(Led_TypeDef Led)
{
	GPIO_PORT[Led]->BSRR = GPIO_PIN[Led];
}

/**
 * @brief  Turns selected LED Off.
 * @param  Led: Specifies the Led to be set off.
 *   This parameter can be one of following parameters:
 *     @arg LED1
 *     @arg LED2
 * @retval None
 */
void LEDOff(Led_TypeDef Led)
{
	GPIO_PORT[Led]->BRR = GPIO_PIN[Led];
}
